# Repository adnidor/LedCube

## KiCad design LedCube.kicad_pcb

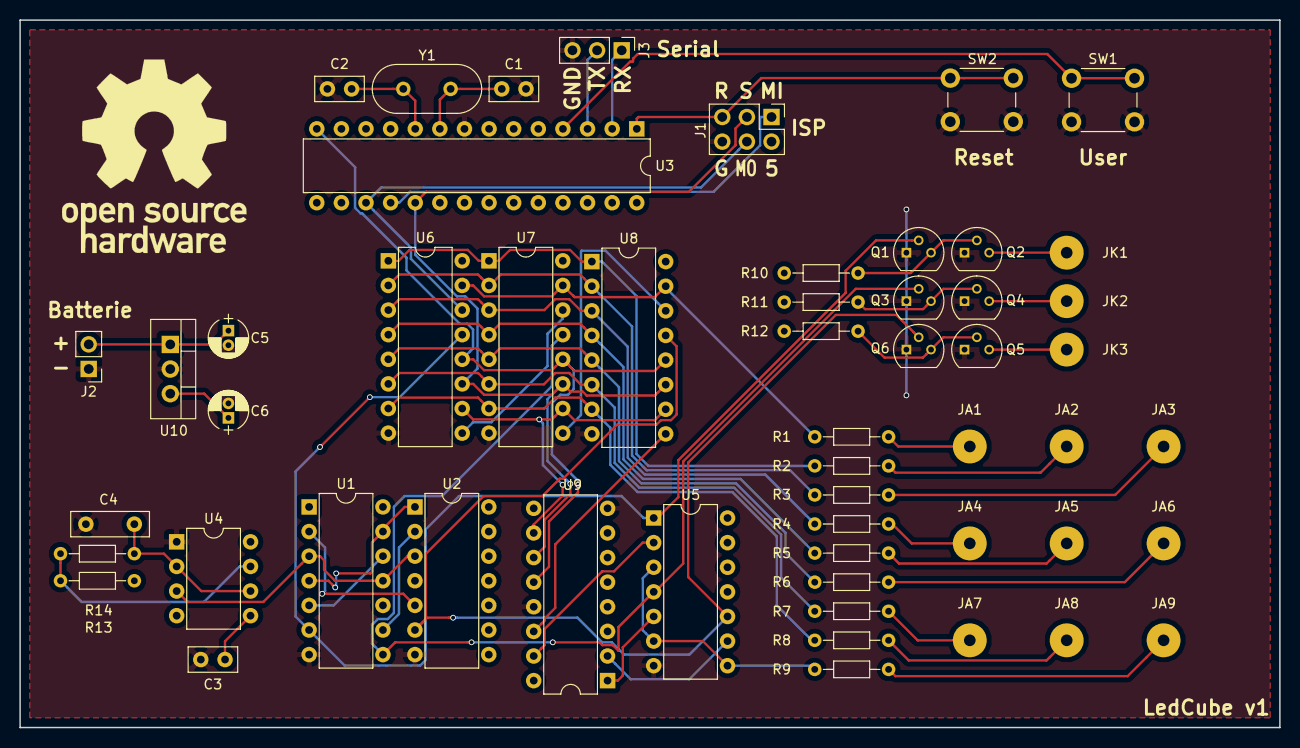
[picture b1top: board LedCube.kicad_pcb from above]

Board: 2 copper layers, 130.0 x 73.0 mm, 54 parts (0 on the bottom side), 55 nets.

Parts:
C1, C2: C; C_Disc_D5.0mm_W2.5mm_P2.50mm
C3: 10nF; C_Disc_D5.0mm_W2.5mm_P2.50mm
C4: 220nF; C_Disc_D8.0mm_W2.5mm_P5.00mm
C5: 330nF; CP_Radial_D4.0mm_P1.50mm
C6: 100nF; CP_Radial_D4.0mm_P1.50mm
J1: Conn_02x03_Odd_Even; Pin_Header_Straight_2x03_Pitch2.54mm
J2: Conn_01x02; Pin_Header_Straight_1x02_Pitch2.54mm
J3: Conn_01x03; Pin_Header_Straight_1x03_Pitch2.54mm
JA1, JA2, JA3, JA4, JA5, JA6, JA7, JA8, JA9: Conn_01x01; SolderWirePad_single_1-2mmDrill
JK1, JK2, JK3: Conn_01x01; SolderWirePad_single_1-2mmDrill
Q1, Q2, Q3, Q4, Q5, Q6: BC557; TO-92_Molded_Narrow
R1, R2, R3, R4, R5, R6, R7, R8, R9: R; R_Axial_DIN0204_L3.6mm_D1.6mm_P7.62mm_Horizontal
R10, R11, R12: 330; R_Axial_DIN0204_L3.6mm_D1.6mm_P7.62mm_Horizontal
R13, R14: 56k; R_Axial_DIN0204_L3.6mm_D1.6mm_P7.62mm_Horizontal
SW1, SW2: SW_Push; SW_PUSH_6mm_h5mm
U1, U2: 74HC74; DIP-14_W7.62mm
U3: ATMEGA8-16PU; DIP-28_W7.62mm
U4: LM555; DIP-8_W7.62mm
U5: 74LS125; DIP-14_W7.62mm
U6, U7, U8, U9: 74HC595; DIP-16_W7.62mm
U10: L7805; TO-220_Vertical
Y1: Crystal; Crystal_HC49-U_Vertical

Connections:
+5V: C6.1, J1.2, R10.1, R11.1, R12.1, R13.1, U1.14, U2.14, U3.7, U4.4, U4.8, U5.14, U6.16, U7.16, U8.16, U9.16, U10.3
+9V: C5.1, J2.2, U10.1
/A1: R1.2, U6.15, U7.15, U8.15
/A2: R2.2, U6.1, U7.1, U8.1
/A3: R3.2, U6.2, U7.2, U8.2
/A4: R4.2, U6.3, U7.3, U8.3
/A5: R5.2, U6.4, U7.4, U8.4
/A6: R6.2, U6.5, U7.5, U8.5
/A7: R7.2, U6.6, U7.6, U8.6
/A8: R8.2, U6.7, U7.7, U8.7
/A9: R9.2, U5.3, U5.6, U5.8
/L1_EN: Q1.2, U1.6, U5.1, U6.13
/L2_EN: Q3.2, U1.8, U5.4, U7.13
/L3_EN: Q6.2, U2.6, U5.10, U8.13
/LCLK: U1.3, U1.11, U2.3, U4.3
/MISO: J1.1, U3.18
/MOSI: J1.4, U3.17, U6.14
/RCLK: U3.14, U6.12, U7.12, U8.12, U9.12
/RESET_AVR: J1.5, SW2.2, U3.1
/RESET_RC: U1.4, U1.13, U2.1
/RESET_SR: U6.10, U7.10, U8.10, U9.10
/SCLK: J1.3, U3.19, U6.11, U7.11, U8.11, U9.11
GND: C1.2, C2.2, C3.2, C4.2, C5.2, C6.2, J1.6, J2.1, J3.3, Q1.1, Q2.1, Q3.1, Q4.1, Q5.1, Q6.1, SW1.2, SW2.1, U1.7, U2.7, U3.8, U4.1, U5.7, U6.8, U7.8, U8.8, U9.8, U9.13, U10.2
unnamed: C1.1, U3.9, Y1.1
unnamed: C2.1, U3.10, Y1.2
unnamed: C3.1, U4.5
unnamed: C4.1, R14.2, U4.2, U4.6
unnamed: J3.1, U3.2
unnamed: J3.2, U3.3
unnamed: JA1.1, R1.1
unnamed: JA2.1, R2.1
unnamed: JA3.1, R3.1
unnamed: JA4.1, R4.1
unnamed: JA5.1, R5.1
unnamed: JA6.1, R6.1
unnamed: JA7.1, R7.1
unnamed: JA8.1, R8.1
unnamed: JA9.1, R9.1
unnamed: JK1.1, Q2.3
unnamed: JK2.1, Q4.3
unnamed: JK3.1, Q5.3
unnamed: Q1.3, Q2.2, R10.2
unnamed: Q3.3, Q4.2, R11.2
unnamed: Q5.2, Q6.3, R12.2
unnamed: R13.2, R14.1, U4.7
unnamed: SW1.1, U3.4
unnamed: U1.2, U2.5
unnamed: U1.9, U2.2
unnamed: U1.5, U1.12
unnamed: U5.2, U9.15
unnamed: U5.5, U9.1
unnamed: U5.9, U9.2
unnamed: U6.9, U7.14
unnamed: U7.9, U8.14
unnamed: U8.9, U9.14

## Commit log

2018-05-10 init
